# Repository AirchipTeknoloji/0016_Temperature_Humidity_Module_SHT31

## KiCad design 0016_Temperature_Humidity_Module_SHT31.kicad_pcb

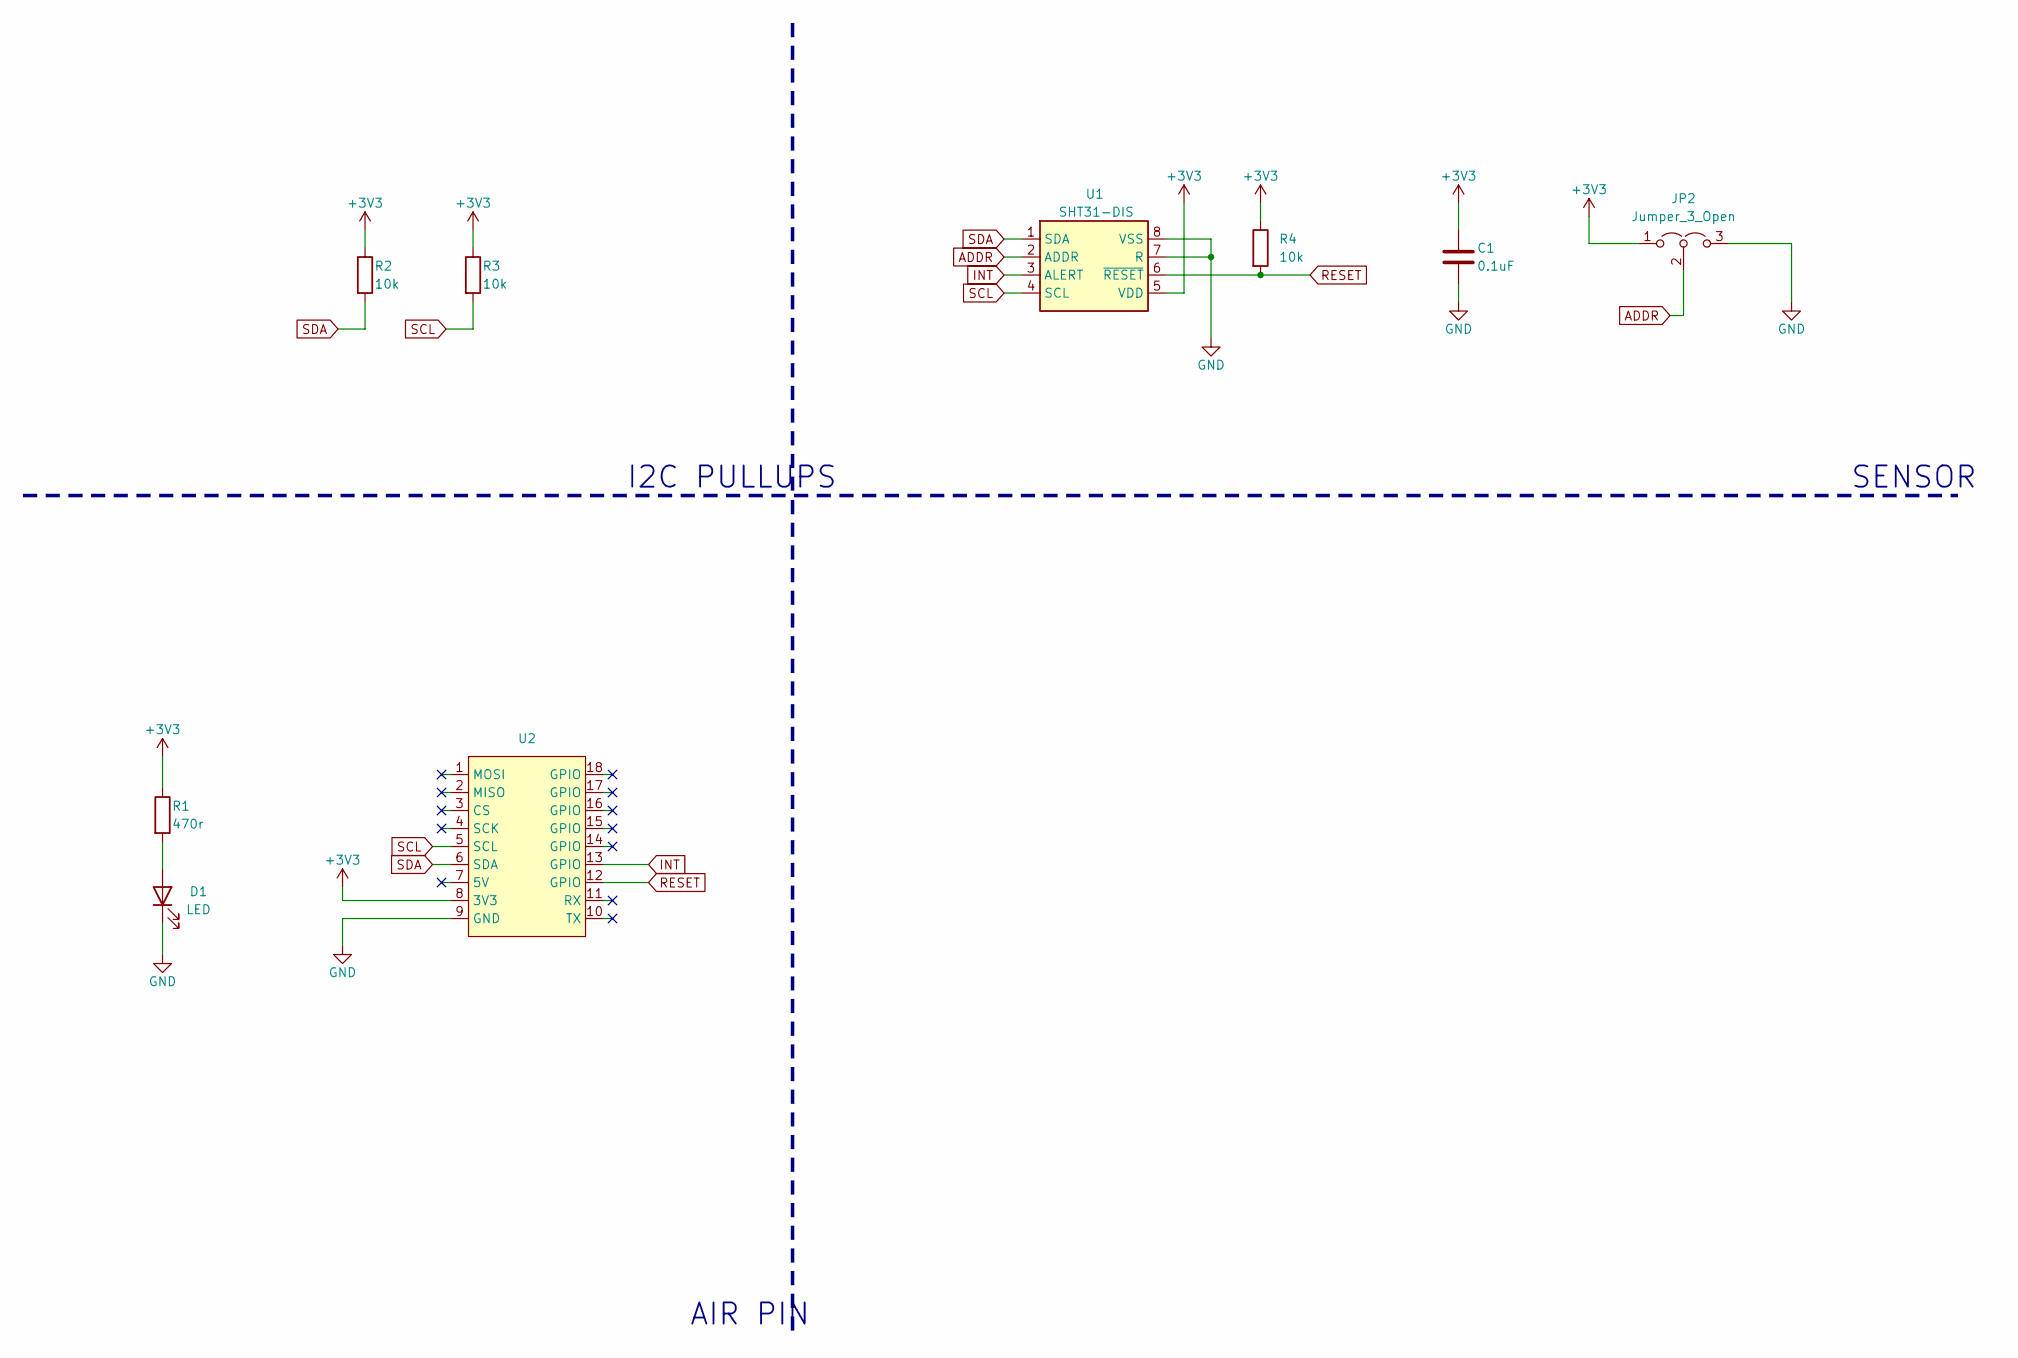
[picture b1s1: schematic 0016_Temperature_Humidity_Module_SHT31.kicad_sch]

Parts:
C1: 0.1uF; C_0805_2012Metric
D1: LED; LED_0805_2012Metric
JP2: Jumper_3_Open; SolderJumper-3_P1.3mm_Open_Pad1.0x1.5mm
R1: 470r; R_0805_2012Metric
R2, R3, R4: 10k; R_0805_2012Metric
U1: SHT31-DIS; Sensirion_DFN-8-1EP_2.5x2.5mm_P0.5mm_EP1.1x1.7mm
U2: air_module

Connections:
+3V3: C1.1, JP2.1 (A), R1.1, R2.1, R3.1, R4.1, U1.5 (VDD), U2.8 (3V3)
ADDR: JP2.2 (C), U1.2 (ADDR)
GND: C1.2, D1.1 (K), JP2.3 (B), U1.7 (R), U1.8 (VSS), U1.9 (VSS), U2.9 (GND)
INT: U1.3 (ALERT), U2.13 (GPIO)
unnamed: D1.2 (A), R1.2
RESET: R4.2, U1.6 (~RESET), U2.12 (GPIO)
SCL: R3.2, U1.4 (SCL), U2.5 (SCL)
SDA: R2.2, U1.1 (SDA), U2.6 (SDA)

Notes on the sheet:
AIR PIN
SENSOR
I2C PULLUPS

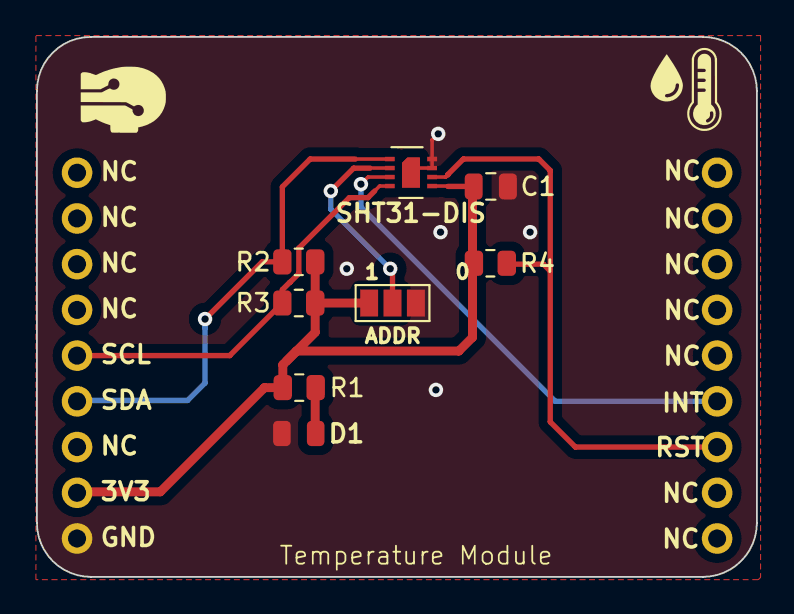
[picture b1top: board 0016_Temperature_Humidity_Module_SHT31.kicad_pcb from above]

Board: 2 copper layers, 40.0 x 30.0 mm, 9 parts (0 on the bottom side), 8 nets.
